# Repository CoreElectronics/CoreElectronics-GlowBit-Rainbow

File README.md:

# Core Electronics GlowBit­™ rainbow
This is the hardware repo for the Core Electronics *GlowBit rainbow*

The [GlowBit™ rainbow](https://core-electronics.com.au/glowbit-rainbow.html) is a beautiful LED display and a *Core Electronics Original* (made right here in Newcastle, Australia). Onboard, there are 13 individually addressable LEDs – all driven by a single IO pin. Alligator + Banana-plug connections make the rainbow a perfect companion for micro:bit or Circuit Playground since there's no soldering required.

Our [getting started guide](https://core-electronics.com.au/tutorials/glowbit-rainbow-quickstart-guide-for-micro-bit.html) covers how to wire-up your rainbow, and six creative, code-along projects to get you started. From there, remix to your heart's content. This is the perfect companion for the micro:bit onboard accelerometer and compass, along with other creative ways to display useful information such as angles, gauges, or colourful patterns on a rainbow.

GlowBit devices use the latest WS2812B v5 technology LEDs which are compatible with existing WS2812 / NeoPixel libraries available for popular development boards.

**Features**
- Works with micro:bit V1 and V2, Circuit Playground, and other maker favourites
- 13x WS2812B-v5 LEDs, compatible with NeoPixel
- Individually controlled LEDs from a single pin
- Connect with alligator clips, banana plugs or the 4pin breakout header
- Protractor inspired artwork - each LED is labelled in 15-degree increments, across a 180-degree curve
- Chainable - the breakout header has a data output so you can daisy-chain multiple rainbows together
- [Quickstart guide and instructions](https://core-electronics.com.au/tutorials/glowbit-rainbow-quickstart-guide-for-micro-bit.html)
- Manufactured and supported in Australia by Core Electronics

# License
This project is open source - please review the LICENSE.md file for further licensing information.

If you have any technical questions, or concerns about licensing, please contact technical support on the [Core Electronics forums](https://forum.core-electronics.com.au/).

*\"GlowBit\" is a trademark of Core Electronics Pty Ltd.*

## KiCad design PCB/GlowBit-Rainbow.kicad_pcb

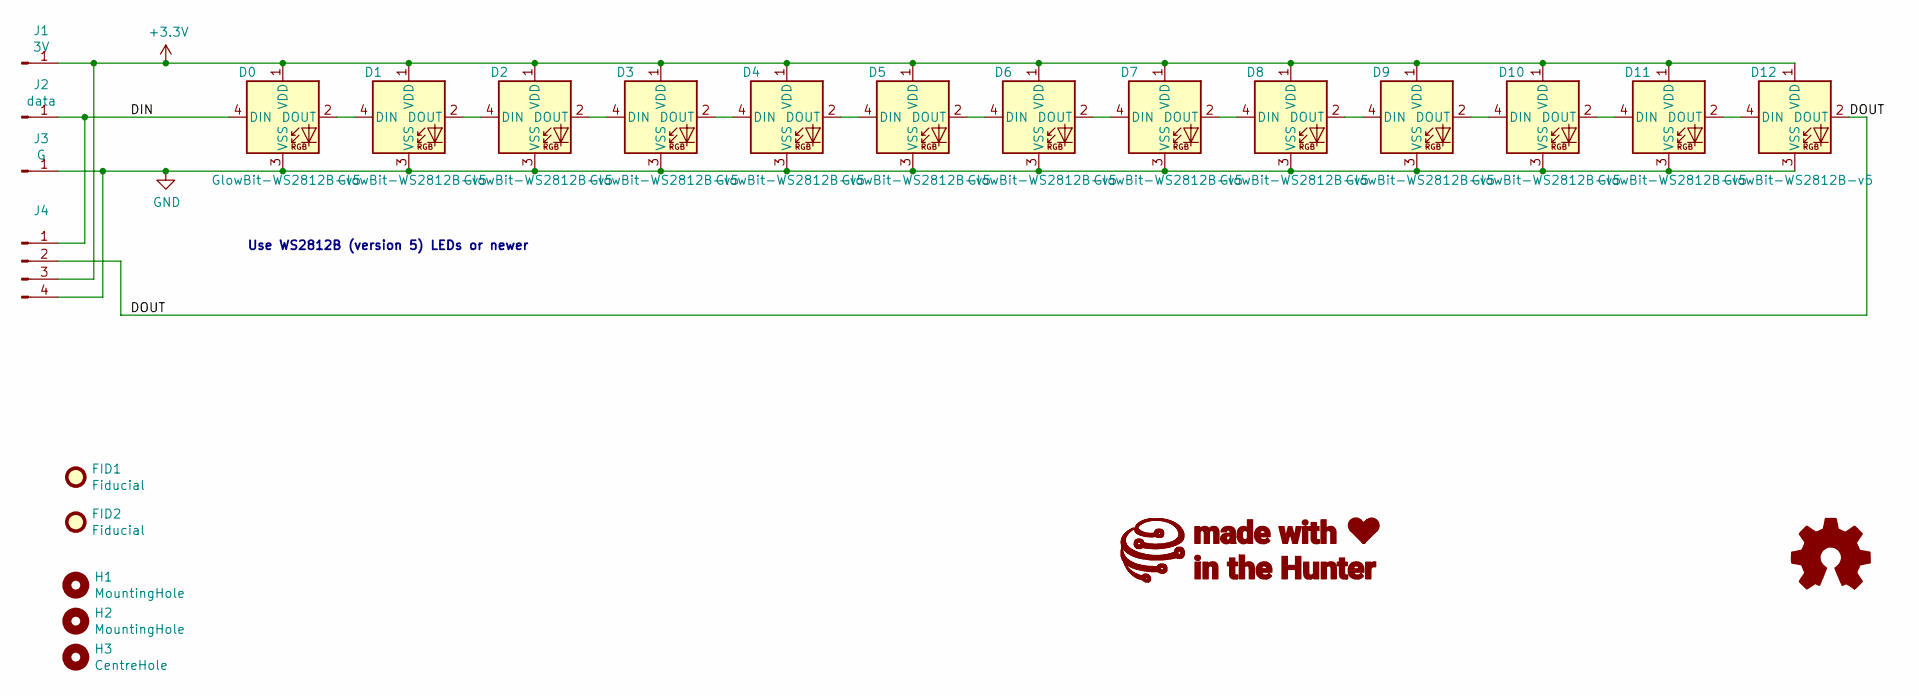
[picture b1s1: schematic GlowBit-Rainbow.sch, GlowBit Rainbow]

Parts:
D0, D1, D2, D3, D4, D5, D6, D7, D8, D9, D10, D11, D12: GlowBit-WS2812B-v5; LED_GlowBit_WS2812B_NoSilk
FID1, FID2: Fiducial; Fiducial_1mm_Mask2mm
G1: LOGO_CoreElectronics_made-with-love; CoreElectronics_made-with-love_26mm
H1, H2: MountingHole; MountingHole_3.2mm_M3
H3: CentreHole; MountingHole_2.1mm
J1: 3V; Conn_alligator-banana
J2: data; Conn_alligator-banana
J3: G; Conn_alligator-banana
J4: PinSocket_1x04_P2.54mm_Vertical
LOGO1: Logo_Open_Hardware_Small; oshw

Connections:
+3V3: D0.1 (VDD), D1.1 (VDD), D2.1 (VDD), D3.1 (VDD), D4.1 (VDD), D5.1 (VDD), D6.1 (VDD), D7.1 (VDD), D8.1 (VDD), D9.1 (VDD), D10.1 (VDD), D11.1 (VDD), D12.1 (VDD), J1.1, J4.3
/DIN: D0.4 (DIN), J2.1, J4.1
/DOUT: D12.2 (DOUT), J4.2
GND: D0.3 (VSS), D1.3 (VSS), D2.3 (VSS), D3.3 (VSS), D4.3 (VSS), D5.3 (VSS), D6.3 (VSS), D7.3 (VSS), D8.3 (VSS), D9.3 (VSS), D10.3 (VSS), D11.3 (VSS), D12.3 (VSS), J3.1, J4.4
unnamed: D0.2 (DOUT), D1.4 (DIN)
unnamed: D1.2 (DOUT), D2.4 (DIN)
unnamed: D2.2 (DOUT), D3.4 (DIN)
unnamed: D3.2 (DOUT), D4.4 (DIN)
unnamed: D4.2 (DOUT), D5.4 (DIN)
unnamed: D5.2 (DOUT), D6.4 (DIN)
unnamed: D6.2 (DOUT), D7.4 (DIN)
unnamed: D7.2 (DOUT), D8.4 (DIN)
unnamed: D8.2 (DOUT), D9.4 (DIN)
unnamed: D10.2 (DOUT), D11.4 (DIN)
unnamed: D9.2 (DOUT), D10.4 (DIN)
unnamed: D11.2 (DOUT), D12.4 (DIN)

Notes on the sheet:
Use WS2812B (version 5) LEDs or newer

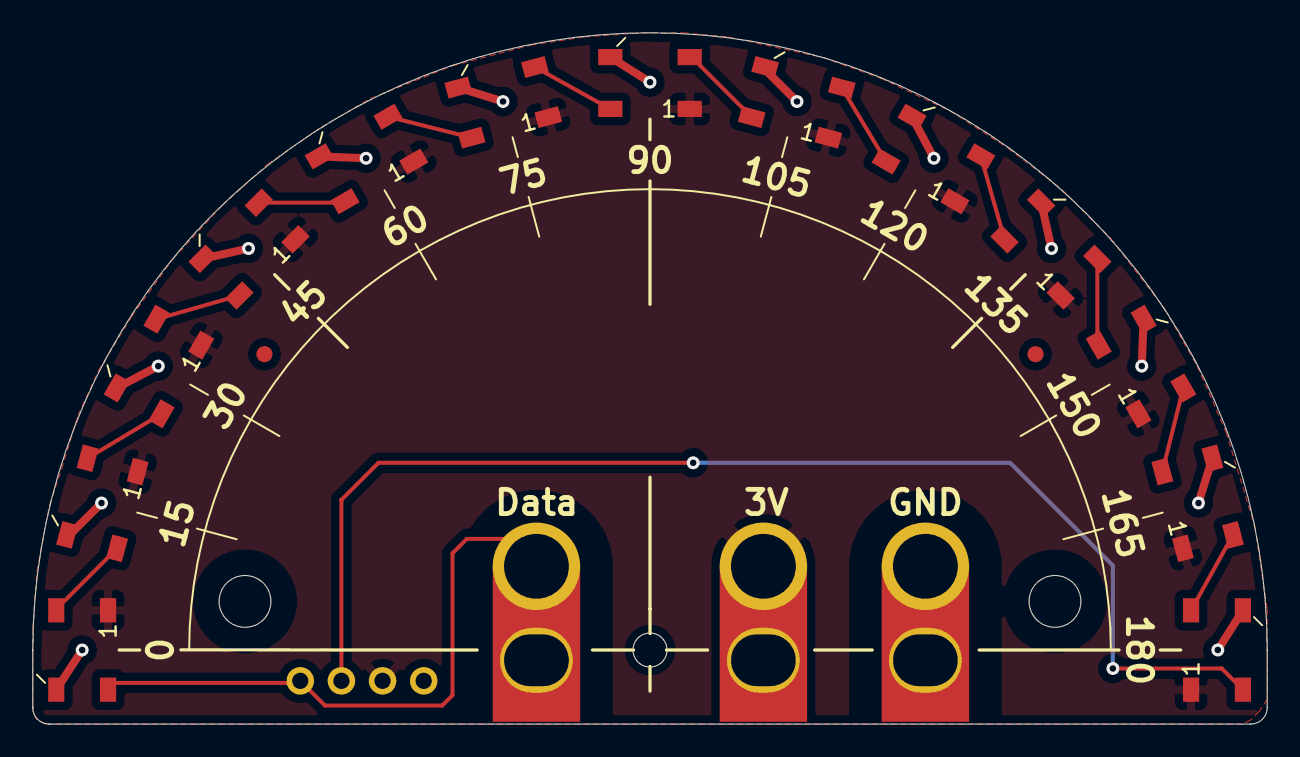
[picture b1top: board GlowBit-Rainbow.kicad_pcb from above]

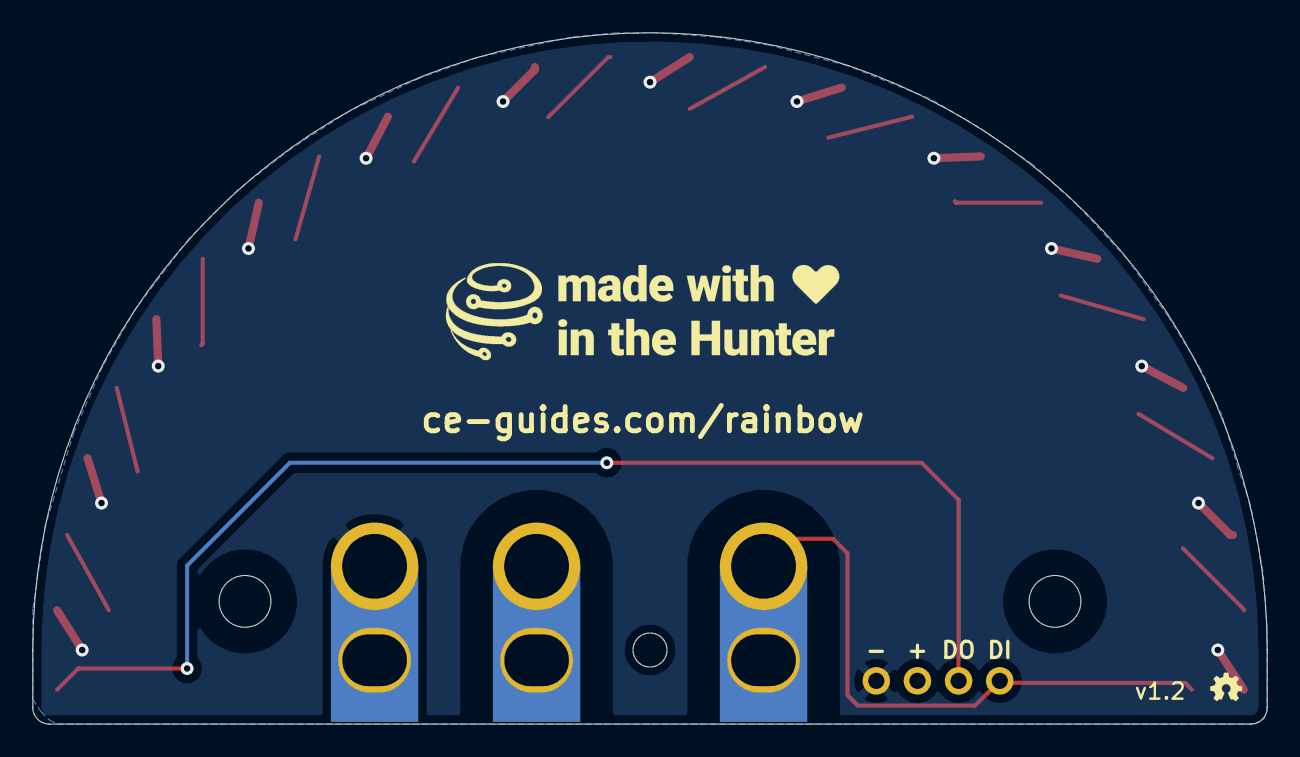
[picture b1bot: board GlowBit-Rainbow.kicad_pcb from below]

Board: 2 copper layers, 76.2 x 42.7 mm, 24 parts (3 on the bottom side), 16 nets.

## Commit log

2021-03-20 deleting rainbow2.jpg
2021-03-20 smaller main image
2021-03-21 Version 1.2
    Correct the rear silk pin labels (DI and DO were swapped in v1.1)

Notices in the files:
PCB/GlowBit-Rainbow.kicad_pcb:
License: CCASAv4.0 https://creativecommons.org/licenses/by-sa/4.0
Released under the Creative Commons Attribution Share-Alike 4.0 License
